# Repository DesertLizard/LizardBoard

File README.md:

# Desert Lizard board
Copyright © 2015 Bart Massey

Welcome to the *Desert Lizard*, an open-hardware open-source
beginner e-jewelry and construction tutorial project!

For details and current status, please see our GitHub [wiki](https://github.com/DesertLizard/LizardBoard/wiki).

## License

The hardware design and source code for this project is
available under the MIT License. See the file COPYING in
this distribution for license terms.

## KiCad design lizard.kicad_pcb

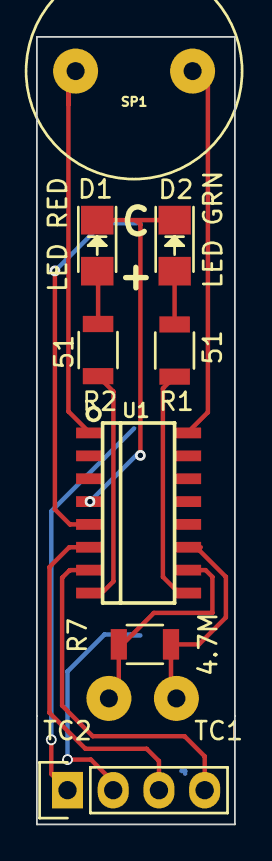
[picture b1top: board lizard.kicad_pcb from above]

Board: 2 copper layers, 11.0 x 43.8 mm, 11 parts (1 on the bottom side), 12 nets.

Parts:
BT1: BATTERY; linx-bat-hld-001
C4: TC1; SolderWirePad_single_1mmDrill
C5: TC2; SolderWirePad_single_1mmDrill
D1: LED RED; LED-1206
D2: LED GRN; LED-1206
P1: DEBUG; Pin_Header_Straight_1x04
R1, R2: 51; R_1206
R7: 4.7M; R_1206
SP1: SPEAKER; PUI-AT-1224-TWT-5V-2-R
U1: EFM8BB1; soic16

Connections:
GND: BT1.2, D1.1, D2.1, P1.1, U1.4
unnamed: C4.1, R7.1, U1.11
unnamed: C5.1, R7.2, U1.10
unnamed: D1.2, R2.1
unnamed: D2.2, R1.1
unnamed: P1.3, U1.6
unnamed: P1.4, U1.7
unnamed: R1.2, U1.9
unnamed: R2.2, U1.8
unnamed: SP1.1, U1.16
unnamed: SP1.2, U1.1
VDD: BT1.1, P1.2, U1.5

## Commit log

2015-06-12 desert lizard board in KiCad
2015-06-12 added README and license
2015-06-13 fixed bugs; added plots
2015-06-13 added KiCAD section to docs
2015-06-15 fixed buglets in pcb
2015-06-21 updated to use extra board size; passed last check
2015-06-21 fixed bugs noticed during OSHPark upload; added packaging script
2015-06-21 fixed bugs noticed during next OSHPark upload
2015-07-02 increased speaker pin hole size; increased back text size
2015-07-04 made improvements to front silk
2015-08-06 finished cheesed redo of schematic and layout for v1.0 production board
    This pass is the first at something that will eventually
    look pretty much like the production PCB. Changes include
    removing all the capacitors as gratuitous, removing the
    gratuitous touchpad resistor, moving the battery to the back
    and enlarging the tabs for hand soldering, moving to the new
    LEDs, and changing to the USB Debug Device compatible debug
2015-08-06 fixed LED resistor values; fixed silk values; misc fixes
2015-08-08 fixed LED resistor values; removed voltage divider; cleaned up layout
2015-08-09 moved most of README onto wiki
2015-08-10 added + and C for diodes
2015-08-10 moved some more stuff on silk; updated art
2015-08-12 did relayout for new battery holder; shrunk board dramatically; simplified layout
2015-08-12 made minor tweaks to layout pre-cut
2015-08-17 prepped for OSH Park; need to fix battery ground
2015-08-17 modified battery ground to fit board
2015-08-17 replaced battery ground fill covered by mask with big rectangular pad

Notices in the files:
lizard.kicad_pcb:
Open Hardware: see repo for license terms
